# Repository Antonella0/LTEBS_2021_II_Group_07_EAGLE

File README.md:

# LTEBS_2021_II_Group_07_EAGLE
<h3> Group_07: Buquicchio Antonella, Di Liddo Mauro </h3>

<p> This folder contains all the files required for the first assignment. In particular you can find:
<u>
<li> The Library with the new components, TMUX1208 and TCA9546A
<li> The Schematic
<li> The Board
<li> The Design rules
<li> gitignore file </li>
</p>

<h3> Library: Group_07_Library.lbr </h3>
<p> In the library file are contained the two new components which are used in the schematic and in the board. For each device is present the symbol, the footprint and a
briefly description of the device itself. All the information are extracted from the datasheets of Texas Instruments:
<li> TMUX1208: the available package is QFN-16
<li> TCA9546A: the available package is TSSOP-16 </li>
</p>

<p> <b>Note_1</b>: In the TMUX1208, the association between pins of the symbol and pads of the footprint follows the QFN-16 one.</p>

<p> <b>Note_2</b>: The pads of the two components are realized with a rectangular shape without any roundness at the corners. </p>

</p>
<p> The graphical pins disposition of the TMUX1208 and TCA9546A is reorganized with respect to the one provided by the datasheets in order 
to allow an easier connection with the other components in the schematic.
</p>

</p>
<p> In addition to our library, we have used the SparkFun Library (https://github.com/sparkfun/SparkFun-Eagle-Libraries) and the CY8CKIT-059 Library 
(https://github.com/dado93/Cypress-Eagle). </p>

<h3>Schematic: Group_07.sch </h3>
<p> We have created the schematic starting from the given one and the list of components. It is arranged in one page.</p>

<h3>Board: Group_07.brd </h3>
<p> All the components are organized in the top layer. We have used traces width of 10 mils as requested with the exception of the TMUX1208 traces: indeed, the pads 
are very closed each others and, in order to respect the clearance requirements, we have decided to use 8 mils traces. 
</p>

<h3>Design Rules: Group_07.dru </h3>
<p>In order to decide the design rules, we have refered to the requirements of MDsrl (https://www.mdsrl.it/mddesignrules.html).
</p>

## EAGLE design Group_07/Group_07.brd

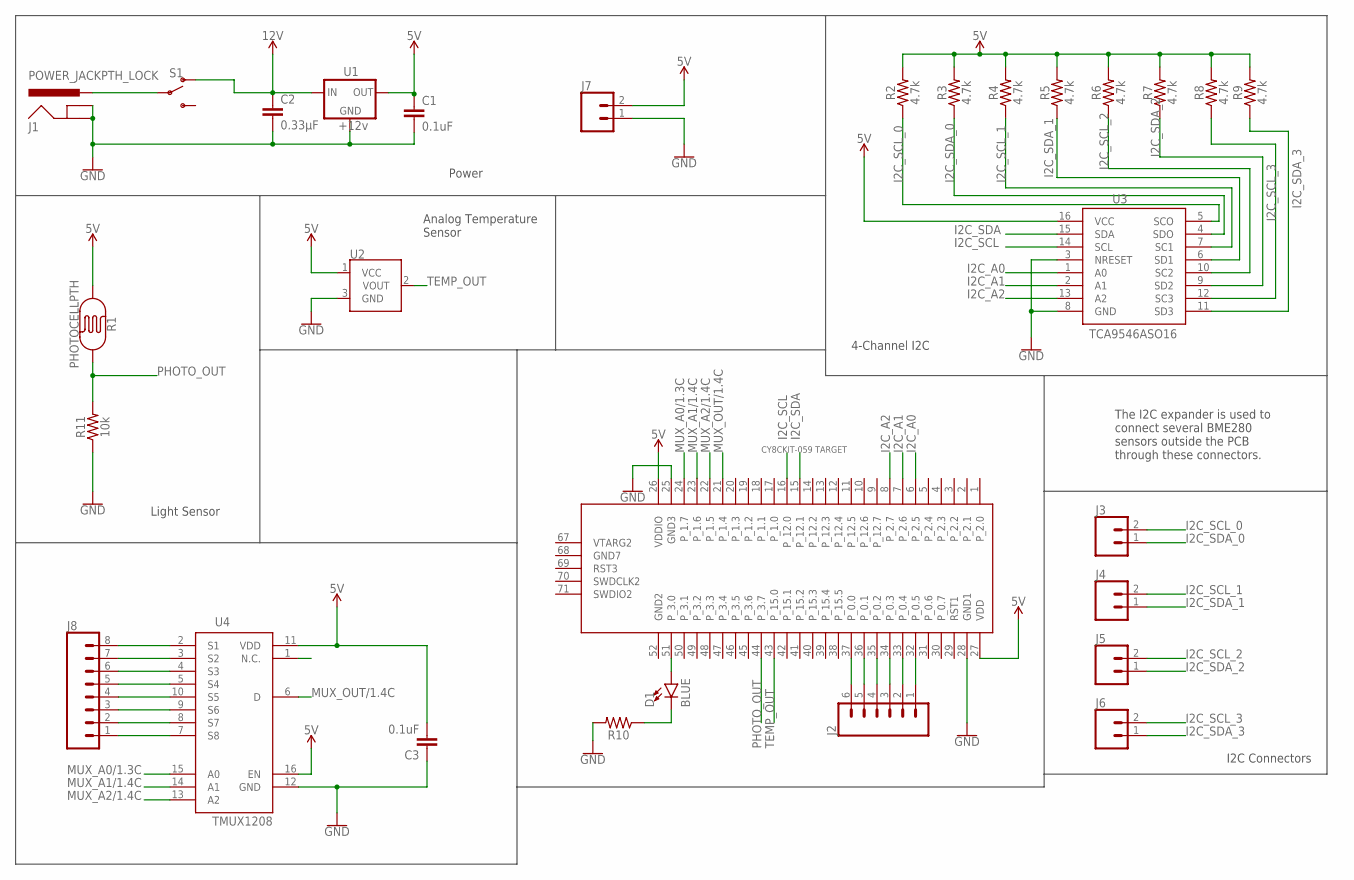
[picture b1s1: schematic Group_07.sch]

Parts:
C1, C3: 0.1uF; CAP-PTH-SMALL-KIT
C2: 0.33µF; 0805
D1: BLUE; LED-1206
J1: POWER_JACKPTH_LOCK; POWER_JACK_PTH_LOCK
J2: CONN_06LOCK; 1X06_LOCK
J3, J4, J5, J6, J7: CONN_02; 1X02
J8: CONN_08LOCK; 1X08_LOCK
R1: PHOTOCELLPTH; PHOTOCELL
R2, R3, R4, R5, R6, R7, R8, R9: 4.7k; 0603
R10: AXIAL-0.3
R11: 10k; 0603
S1: SWITCH-SPDT-PTH-11.6X4.0MM; SWITCH_SPDT_PTH_11.6X4.0MM
U1: +12v; TO-252
U2: TMP36GT9; TO-92
U3: TCA9546ASO16; TSSOP16
U4: TMUX1208; QFN16
U$1: CY8CKIT-059_TARGET

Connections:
5V: C1.1, C3.2, J7.2, R1.1, R2.2, R3.2, R4.2, R5.2, R6.2, R7.2, R8.2, R9.2, U1.2 (OUT), U2.1 (VCC), U3.16 (VCC), U4.11 (VDD), U$1.27 (VDD)
12V: C2.1, S1.1 (O), U1.1 (IN)
GND: C1.2, C2.2, C3.1, J1.GND, J1.GNDBREAK, J7.1, R10.P$2 (2), R11.1, U1.3 (GND), U2.3 (GND), U3.3 (NRESET), U3.8 (GND), U4.12 (GND), U$1.25 (GND3)
I2C_A0: U3.1 (A0), U$1.6 (P_2.5)
I2C_A1: U3.2 (A1), U$1.7 (P_2.6)
I2C_A2: U3.13 (A2), U$1.8 (P_2.7)
I2C_SCL: U3.14 (SCL), U$1.16 (P_12.0)
I2C_SCL_0: J3.2, R2.1, U3.5 (SCO)
I2C_SCL_1: J4.2, R4.1, U3.7 (SC1)
I2C_SCL_2: J5.2, R6.1, U3.10 (SC2)
I2C_SCL_3: J6.2, R8.1, U3.12 (SC3)
I2C_SDA: U3.15 (SDA), U$1.15 (P_12.1)
I2C_SDA_0: J3.1, R3.1, U3.4 (SDO)
I2C_SDA_1: J4.1, R5.1, U3.6 (SD1)
I2C_SDA_2: J5.1, R7.1, U3.9 (SD2)
I2C_SDA_3: J6.1, R9.1, U3.11 (SD3)
MUX_A0/1.3C: U4.15 (A0), U$1.24 (P_1.7)
MUX_A1/1.4C: U4.14 (A1), U$1.23 (P_1.6)
MUX_A2/1.4C: U4.13 (A2), U$1.22 (P_1.5)
MUX_OUT/1.4C: U4.6 (D), U$1.21 (P_1.4)
unnamed: J1.PWR, S1.2
unnamed: J8.8, U4.2 (S1)
unnamed: J2.6, U$1.37 (P_0.0)
unnamed: J2.5, U$1.36 (P_0.1)
unnamed: J2.4, U$1.35 (P_0.2)
unnamed: J2.3, U$1.34 (P_0.3)
unnamed: J2.2, U$1.33 (P_0.4)
unnamed: J2.1, U$1.32 (P_0.5)
unnamed: D1.A, U$1.51 (P_3.0)
unnamed: D1.C, R10.P$1 (1)
unnamed: J8.7, U4.3 (S2)
unnamed: J8.6, U4.4 (S3)
unnamed: J8.5, U4.5 (S4)
unnamed: J8.4, U4.10 (S5)
unnamed: J8.3, U4.9 (S6)
unnamed: J8.2, U4.8 (S7)
unnamed: J8.1, U4.7 (S8)
PHOTO_OUT: R1.2, R11.2, U$1.44 (P_3.7)
TEMP_OUT: U2.2 (VOUT), U$1.43 (P_15.0)

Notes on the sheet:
The I2C expander is used to connect several BME280 sensors outside the PCB through these connectors.
Power
Light Sensor
4-Channel I2C
I2C Connectors
Analog Temperature Sensor

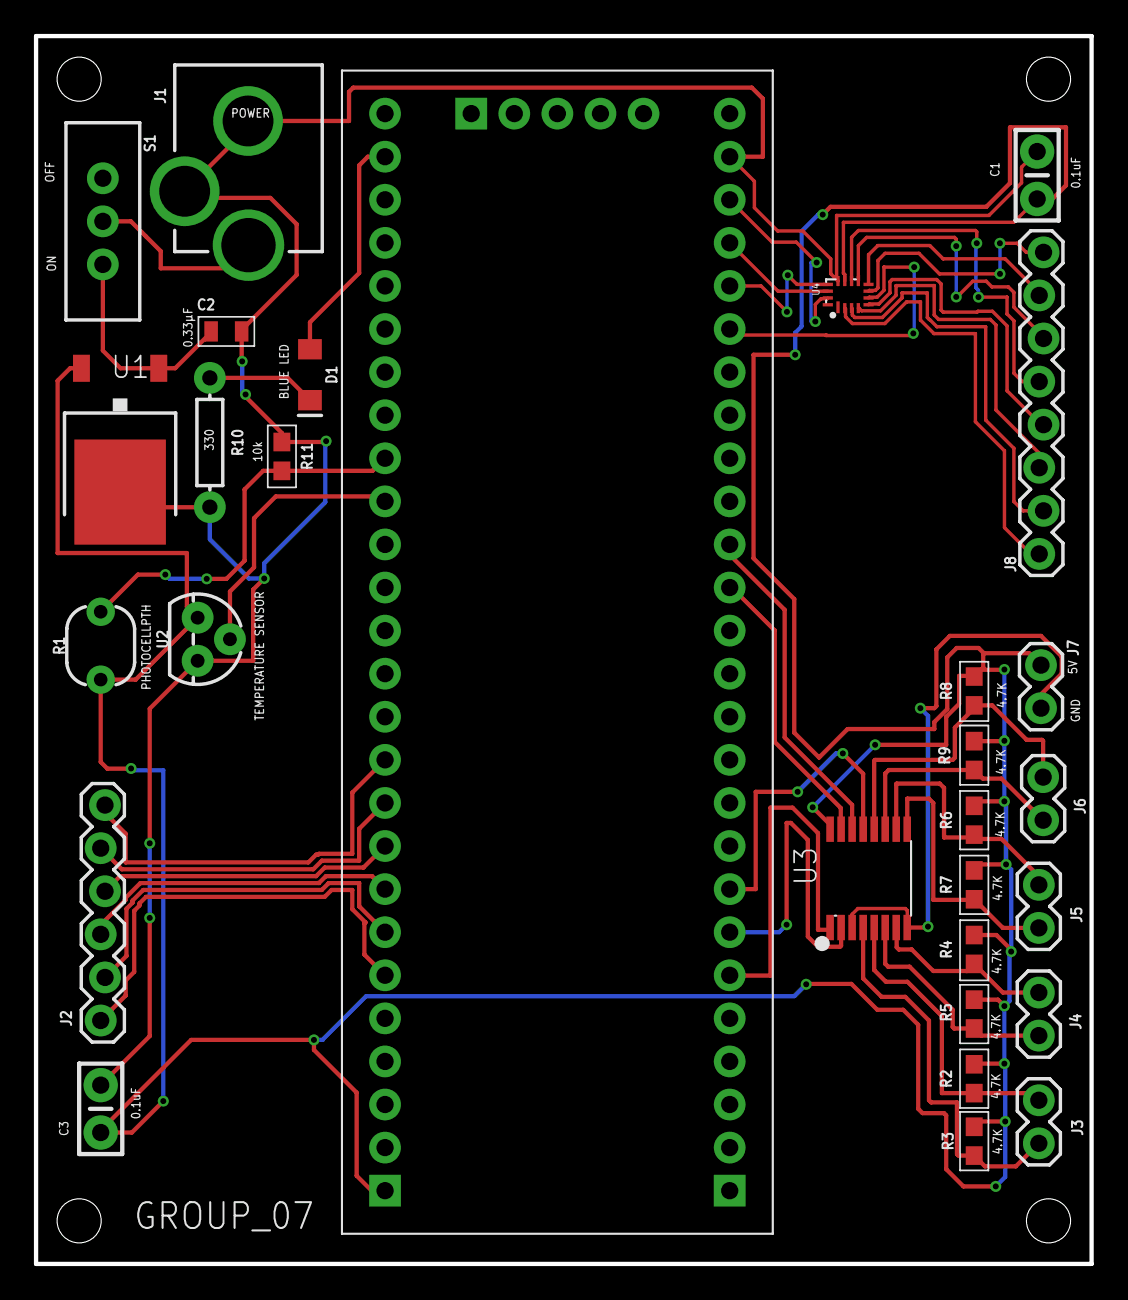
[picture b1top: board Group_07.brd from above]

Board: 2 copper layers, 62.2 x 72.4 mm, 29 parts (0 on the bottom side), 39 nets.

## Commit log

2021-03-19 Changes in the disposition and details
2021-03-19 Adding descriptions
2021-03-19 Description library
2021-03-20 Create .gitignore file
2021-03-20 Backup files
2021-03-20 Revert "Backup files" This reverts commit c019932dfd2d236227c1f5919d51fad0ed4b2c4b. git commit -m "Revert changes"
2021-03-20 FootPrint TMUX
2021-03-20 Board start
2021-03-21 Correction in the schematic
2021-03-21 Disposition of the components and traces
2021-03-22 modifica delle dimensioni vias
2021-03-22 airwire da fixare per problemi di clearance
2021-03-22 airwire fixed by replacing w/ width 8 instead of 10
2021-03-22 all fixed w/ width8
2021-03-23 Disposizione modificata
2021-03-23 Connessioni TCA9546A
2021-03-23 modifiche tmux
2021-03-23 modifica lato sx board
2021-03-23 modifica dimensioni traces
2021-03-23 controllo ratsnest
2021-03-23 aggiunta traces alimentazione e massa
2021-03-23 risoluzione conflitti drc MD S.R.L.
2021-03-24 Modifiche traces GND
2021-03-24 Setting per DRC
2021-03-24 Controllo DRC
2021-03-24 aggiunta primi nomi componenti, holes e modifica descrizione DRC
2021-03-25 Silkscreen
2021-03-25 riduzione dimensioni board e riposizionamento componenti con verifica dru
2021-03-25 Modifica silkscreen, mask and DRC check
2021-03-25 Modifica DRC
2021-03-25 Holes e controllo traces
2021-03-26 correzione holes
2021-03-26 Create README.md
    Add README file
2021-03-26 Creazione cartella
2021-03-26 Final version

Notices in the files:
parts and their libraries:
SparkFun-Aesthetics: Licensing: Creative Commons ShareAlike 4.0 International - https://creativecommons.org/licenses/by-sa/4.0
